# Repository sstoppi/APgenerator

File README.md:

# ap-eap-generator
Open Source Project for an AP an EAP signal generator

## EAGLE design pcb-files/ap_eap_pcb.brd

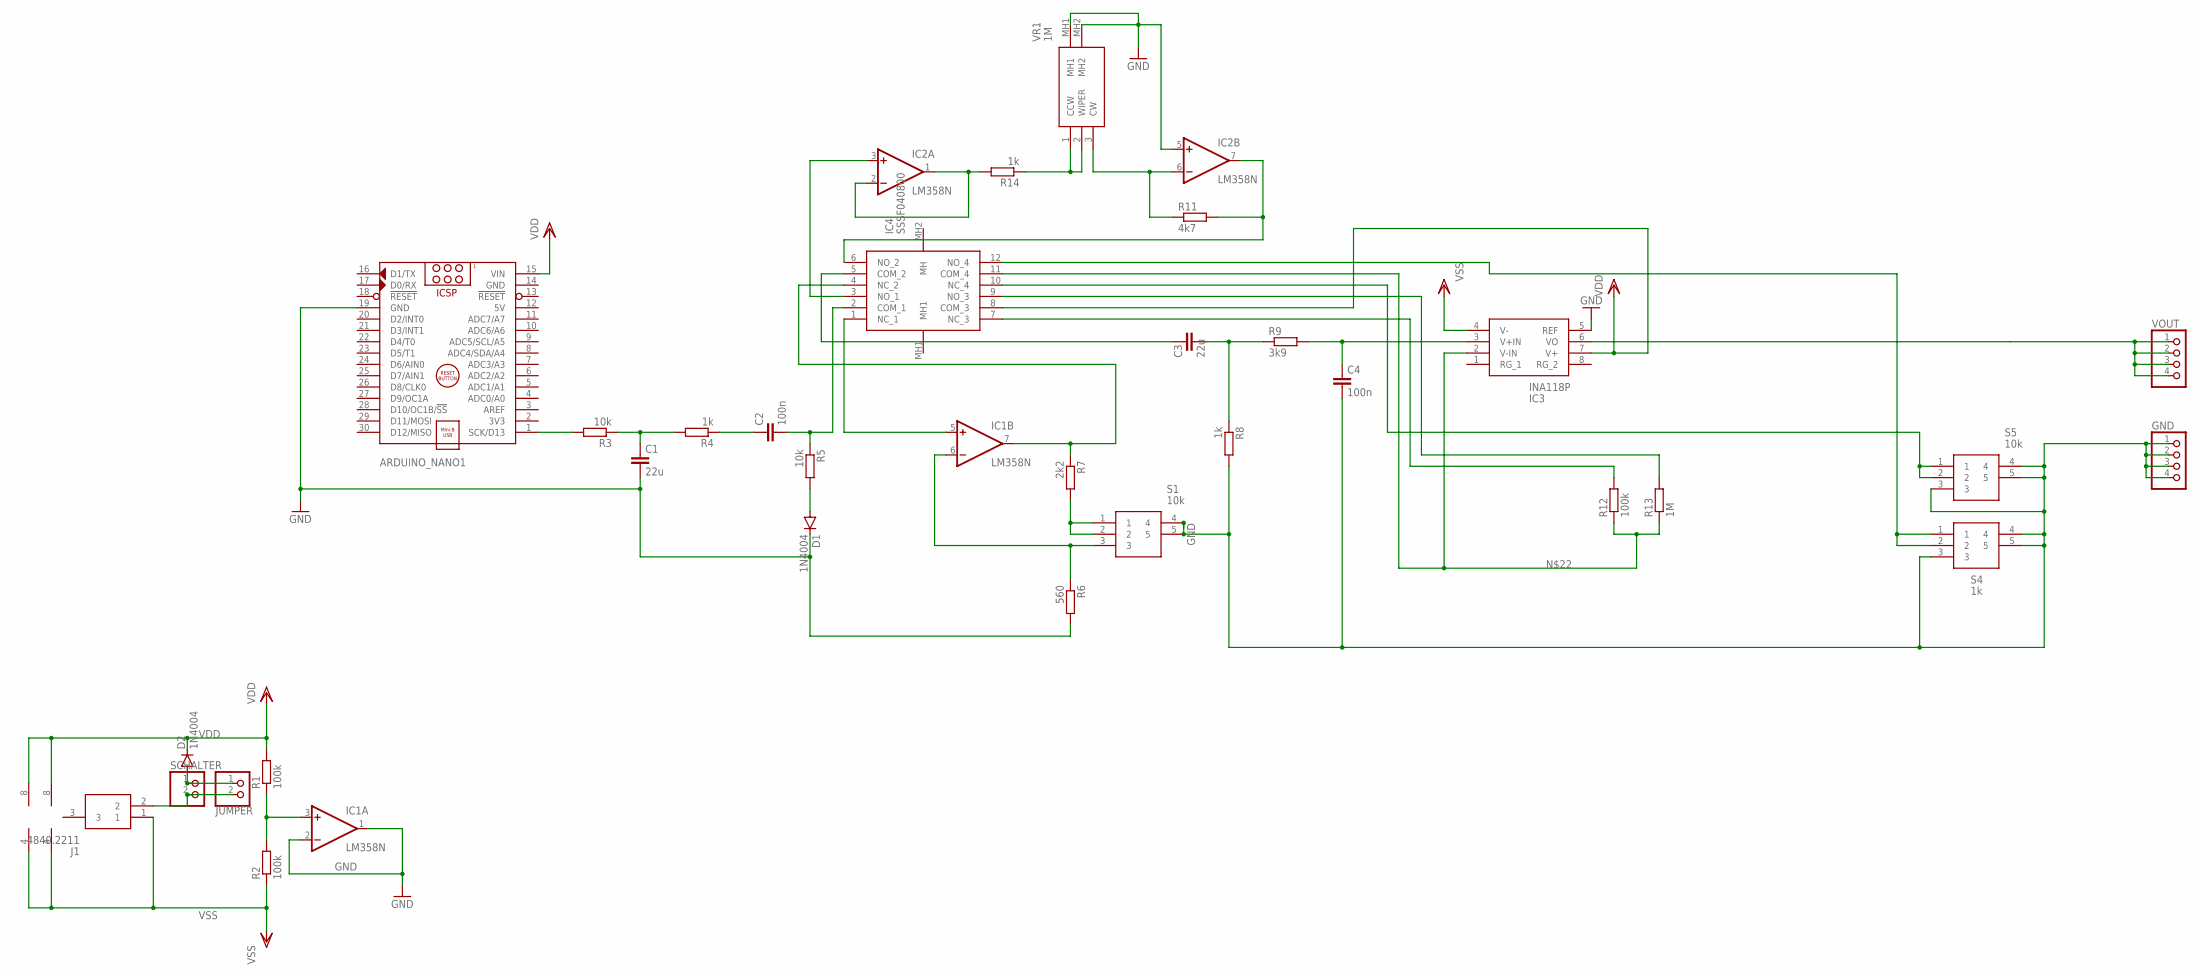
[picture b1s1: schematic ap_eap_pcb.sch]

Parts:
ARDUINO_NANO1: ARDUINO_NANO
C1: 22u; C025-024X044
C2: 100n; C050-024X044
C3: 22u; C025-050X050
C4: 100n; C025-024X044
D1, D2: 1N4004; DO41-10
GND: PINHD-1X4; 1X04
IC1, IC2: LM358N; DIL08
IC3: INA118P; DIP794W53P254L959H508Q8N
IC4: SSSF040800
J1: 4840.2211; 48402211
JUMPER: PINHD-1X2; 1X02
R1, R2, R12: 100k; 0309/12
R3, R5: 10k; 0309/12
R4, R8, R14: 1k; 0309/12
R6: 560; 0309/12
R7: 2k2; 0309/12
R9: 3k9; 0309/12
R11: 4k7; 0309/12
R13: 1M; 0309/12
S1, S5: 10k; PTV09A4020FB103
S4: 1k; PTV09A4020FB103
SCHALTER: PINHD-1X2; 1X02
VOUT: PINHD-1X4; 1X04
VR1: 1M; RV09AF4020KA1M

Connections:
5V: ARDUINO_NANO1.12 (5V)
GND: ARDUINO_NANO1.14 (GND), ARDUINO_NANO1.19 (GND), C1.2, C4.2, D1.C, GND.1, GND.2, GND.3, GND.4, IC1.1 (OUT), IC1.2 (-IN), IC2.5 (+IN), IC3.5 (REF), R6.2, R8.2, S1.4, S1.5, S4.3, S4.4, S4.5, S5.3, S5.4, S5.5, VR1.MH1, VR1.MH2
unnamed: C1.1, R3.1, R4.2
unnamed: IC1.3 (+IN), R1.1, R2.2
unnamed: ARDUINO_NANO1.1 (SCK/D13), R3.2
unnamed: C2.1, R4.1
unnamed: C2.2, IC4.2 (COM_1), R5.1
unnamed: D1.A, R5.2
unnamed: C3.2, R8.1, R9.1
unnamed: IC1.7 (OUT), IC4.4 (NC_2), R7.1
unnamed: R7.2, S1.1, S1.2
unnamed: IC1.6 (-IN), R6.1, S1.3
unnamed: IC1.5 (+IN), IC4.1 (NC_1)
unnamed: C3.1, IC4.5 (COM_2)
unnamed: C4.1, IC3.3 (V+IN), R9.2
unnamed: VOUT.1, VOUT.2, VOUT.3, VOUT.4
unnamed: IC2.3 (+IN), IC4.3 (NO_1)
unnamed: IC2.1 (OUT), IC2.2 (-IN), R14.2
unnamed: IC4.7 (NC_3), R12.2
unnamed: IC2.7 (OUT), IC4.6 (NO_2), R11.2
unnamed: IC2.6 (-IN), R11.1, VR1.3 (CW)
unnamed: IC4.9 (NO_3), R13.2
unnamed: IC3.2 (V-IN), IC4.11 (COM_4), R12.1, R13.1
unnamed: IC4.12 (NO_4), S4.1, S4.2
unnamed: IC4.10 (NC_4), S5.1, S5.2
unnamed: J1.2, JUMPER.2, SCHALTER.2
unnamed: D2.A, JUMPER.1, SCHALTER.1
unnamed: R14.1, VR1.1 (CCW), VR1.2 (WIPER)
VDD: ARDUINO_NANO1.15 (VIN), D2.C, IC1.8 (V+), IC2.8 (V+), IC3.7 (V+), IC4.8 (COM_3), R1.2
VSS: IC1.4 (V-), IC2.4 (V-), IC3.4 (V-), J1.1, R2.1

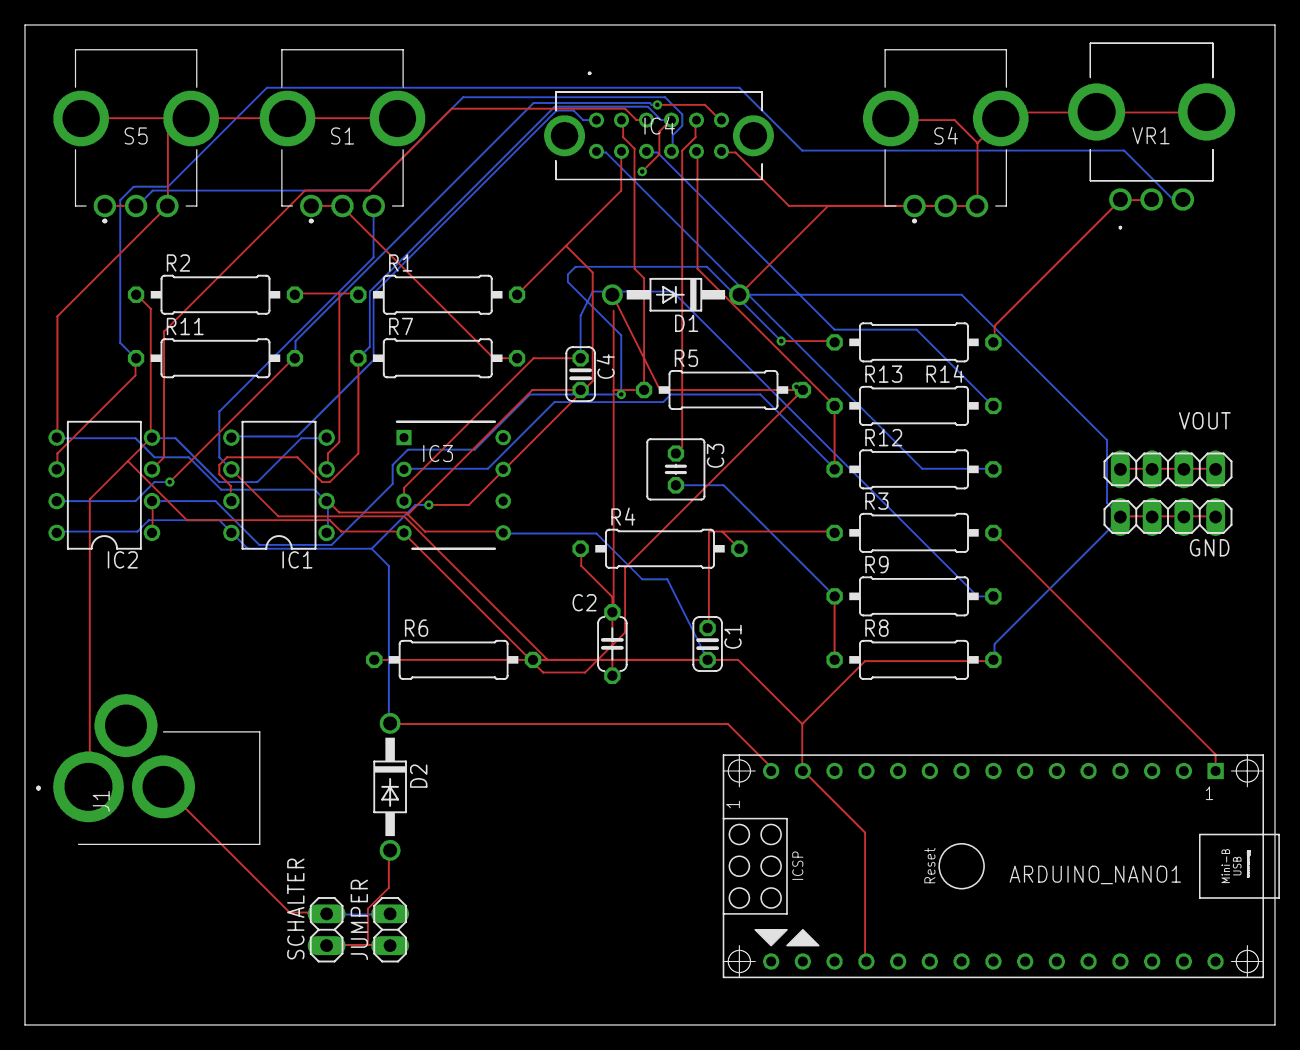
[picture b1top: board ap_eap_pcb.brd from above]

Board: 2 copper layers, 100.0 x 80.0 mm, 33 parts (0 on the bottom side), 29 nets.

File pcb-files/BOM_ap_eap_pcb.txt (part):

Stückliste exportiert aus M:/IHCE-RD/AP Generator/Paper/PCB_design/ap_eap_pcb.sch am 21.01.2022 11:32

Part          Value      Device            Package                  Description                                               DESCRIPTION                                               HEIGHT MANUFACTURER_NAME MANUFACTURER_PART_NUMBER MOUSER_PART_NUMBER   MOUSER_PRICE-STOCK                                                                                        POPULARITY RS_PART_NUMBER RS_PRICE-STOCK                                 SPICEPREFIX
ARDUINO_NANO1            ARDUINO_NANO      ARDUINO_NANO             Arduino Nano V3.0 Module                                                                                                                                                                                                                                                                                                                                                                 
C1            22u        C-EU025-024X044   C025-024X044             CAPACITOR, European symbol                                                                                                                                                                                                                                                                           56                                                                       C          
C2            100n       C-EU050-024X044   C050-024X044             CAPACITOR, European symbol                                                                                                                                                                                                                                                                           33                                                                       C          
C3            22u        C-EU025-050X050   C025-050X050             CAPACITOR, European symbol                                                                                                                                                                                                                                                                           16                                                                       C          
C4            100n       C-EU025-024X044   C025-024X044             CAPACITOR, European symbol                                                                                                                                                                                                                                                                           56                                                                       C          
D1            1N4004     1N4004            DO41-10                  DIODE                                                                                                                                                                                                                                                                                                82                                                                                  
D2            1N4004     1N4004            DO41-10                  DIODE                                                                                                                                                                                                                                                                                                82                                                                                  
GND                      PINHD-1X4         1X04                     PIN HEADER                                                                                                                                                                                                                                                                                           91                                                                                  
IC1           LM358N     LM358N            DIL08                    OP AMP also LM158; LM258; LM2904                                                                                                                                                                                                                                                                     7                                                                                   
IC2           LM358N     LM358N            DIL08                    OP AMP also LM158; LM258; LM2904                                                                                                                                                                                                                                                                     7                                                                                   
IC3           INA118P    INA118P           DIP794W53P254L959H508Q8N INA118P, Instrumentation Amplifier, 73dB CMRR, 8-Pin PDIP INA118P, Instrumentation Amplifier, 73dB CMRR, 8-Pin PDIP 5.08mm Texas Instruments INA118P                  595-INA118P          https://www.mouser.co.uk/ProductDetail/Texas-Instruments/INA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                                                                                     
IC4           SSSF040800 SSSF040800        SSSF040800               Through Hole Slide Switch 4PDT Maintained 100 mA Slide    Through Hole Slide Switch 4PDT Maintained 100 mA Slide    14.5mm ALPS              SSSF040800                                                                                                                                                         1238902        http://uk.rs-online.com/web/p/products/1238902            
J1            4840.2211  4840.2211         48402211                 DC Power Connectors DC SOCKET 2.35MM PCB MOUNT            DC Power Connectors DC SOCKET 2.35MM PCB MOUNT            11mm   SCHURTER          4840.2211                693-4840.2211        https://www.mouser.co.uk/ProductDetail/Schurter/48402211?qs=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                                                                                                  
JUMPER                   PINHD-1X2         1X02                     PIN HEADER                                                                                                                                                                                                                                                                                           98                                                                                  
R1            100k       R-EU_0309/12      0309/12                  RESISTOR, European symbol                                                                                                                                                                                                                                                                            6                                                                        R          
R2            100k       R-EU_0309/12      0309/12                  RESISTOR, European symbol                                                                                                                                                                                                                                                                            6                                                                        R          
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
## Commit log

2022-01-21 Add files via upload
    Arduino microcontroller file for generating the initial stimulus
2022-01-21 Add files via upload
    simulation data for the AP and EAP stage
2022-01-21 Add files via upload
    ltspice simulation files for the ap and the eap stage
